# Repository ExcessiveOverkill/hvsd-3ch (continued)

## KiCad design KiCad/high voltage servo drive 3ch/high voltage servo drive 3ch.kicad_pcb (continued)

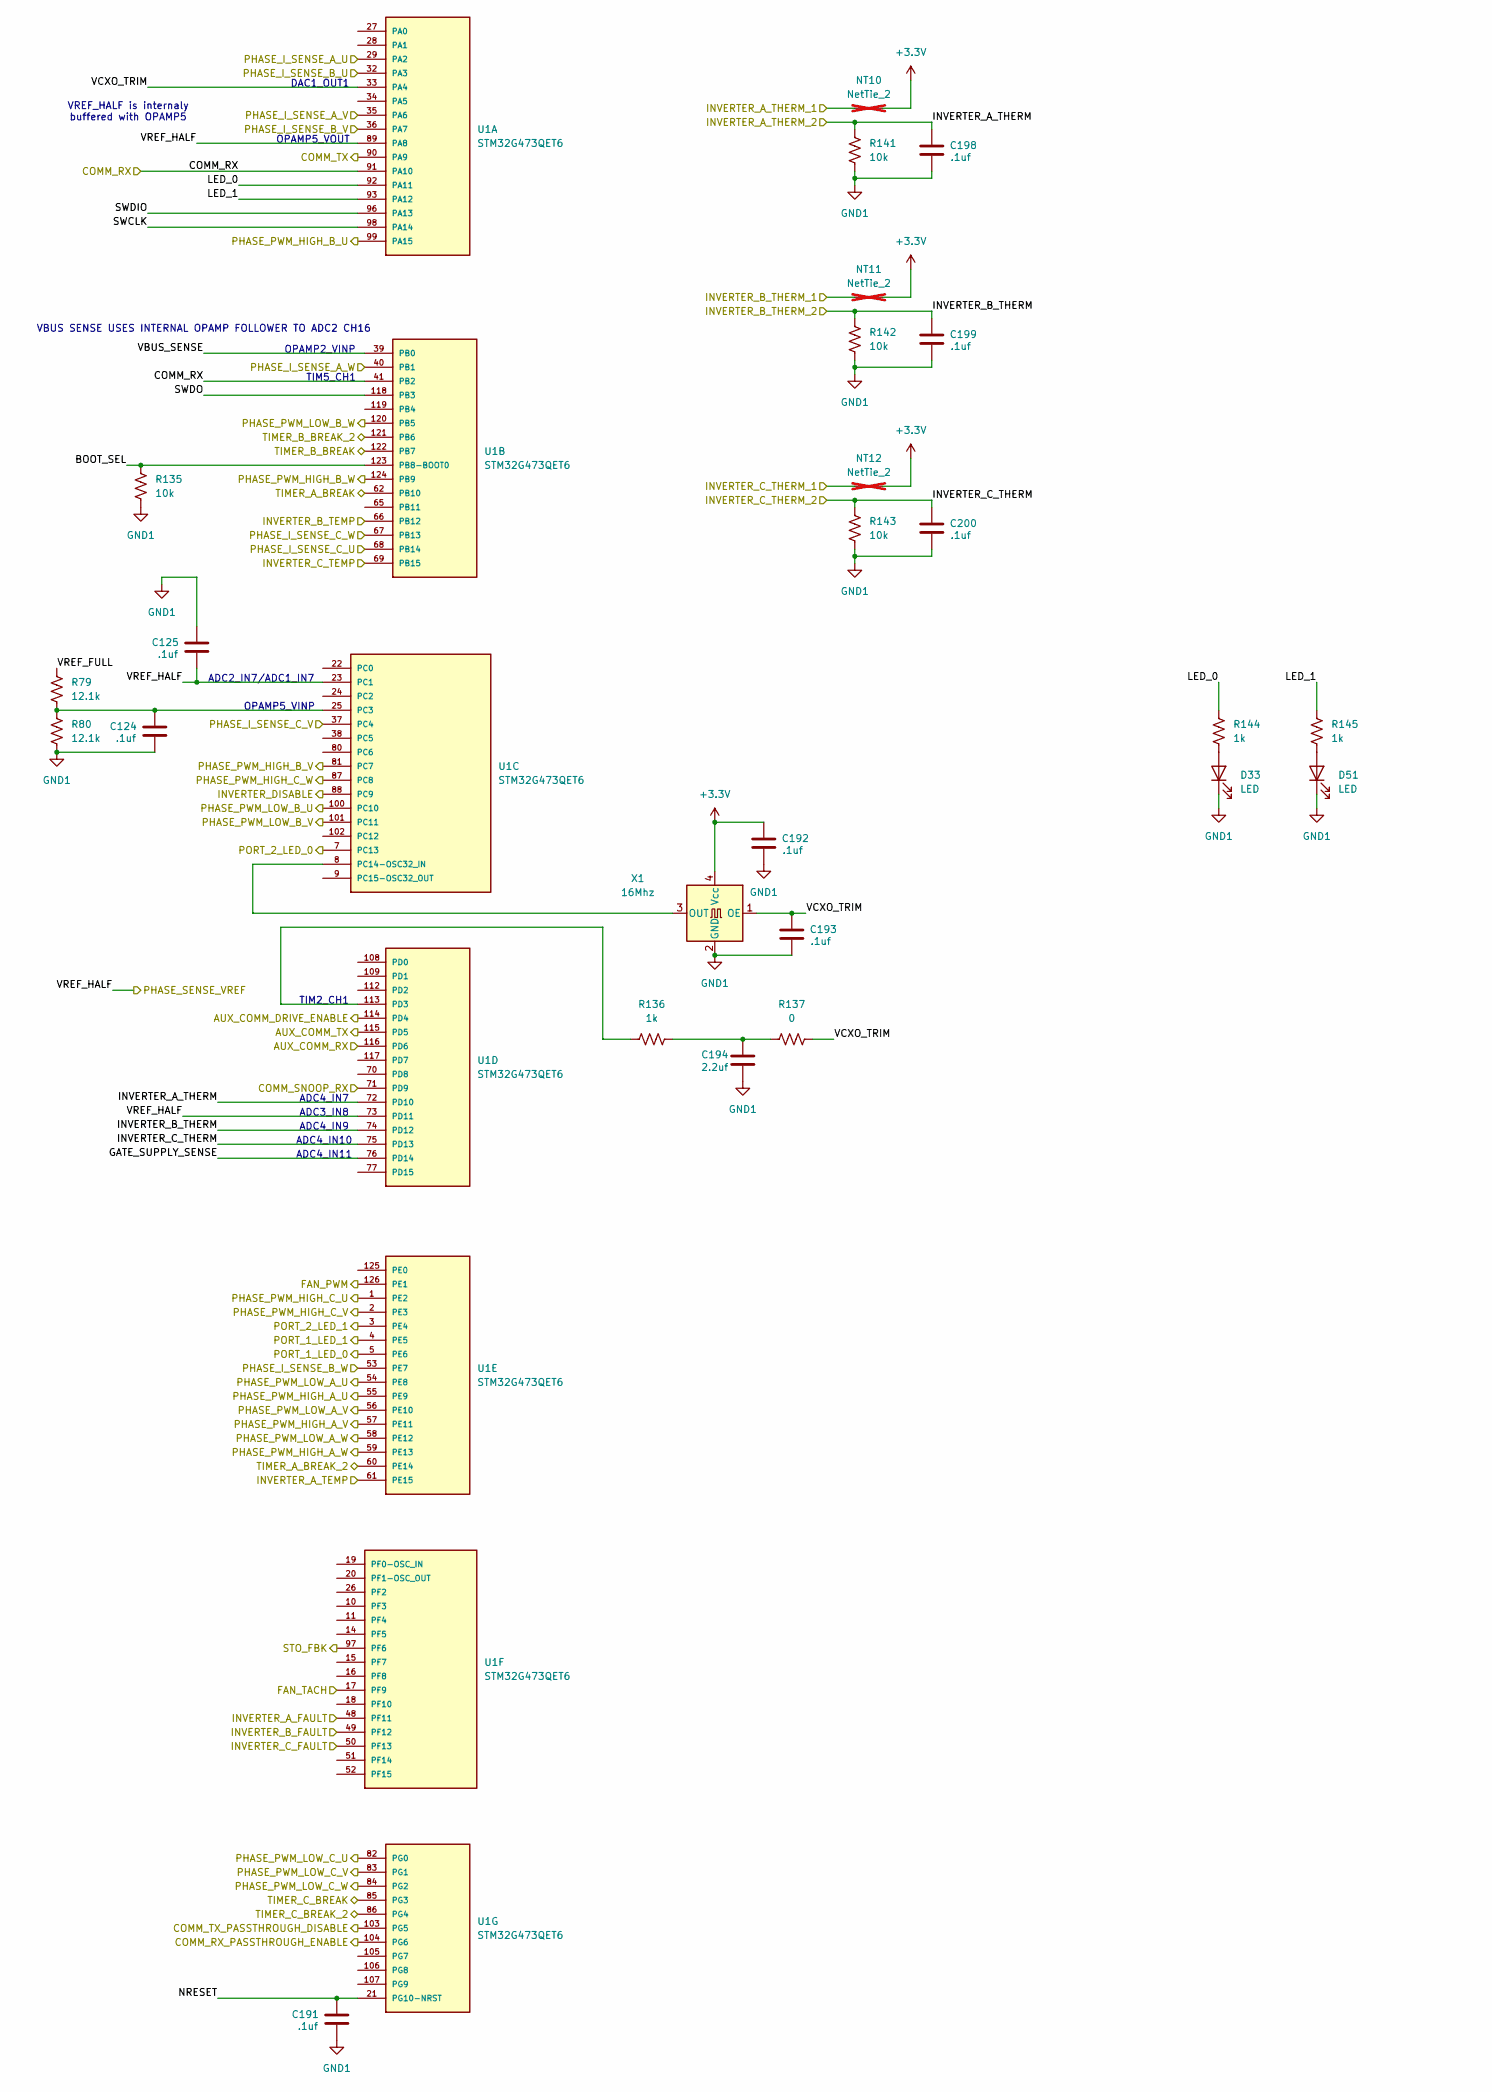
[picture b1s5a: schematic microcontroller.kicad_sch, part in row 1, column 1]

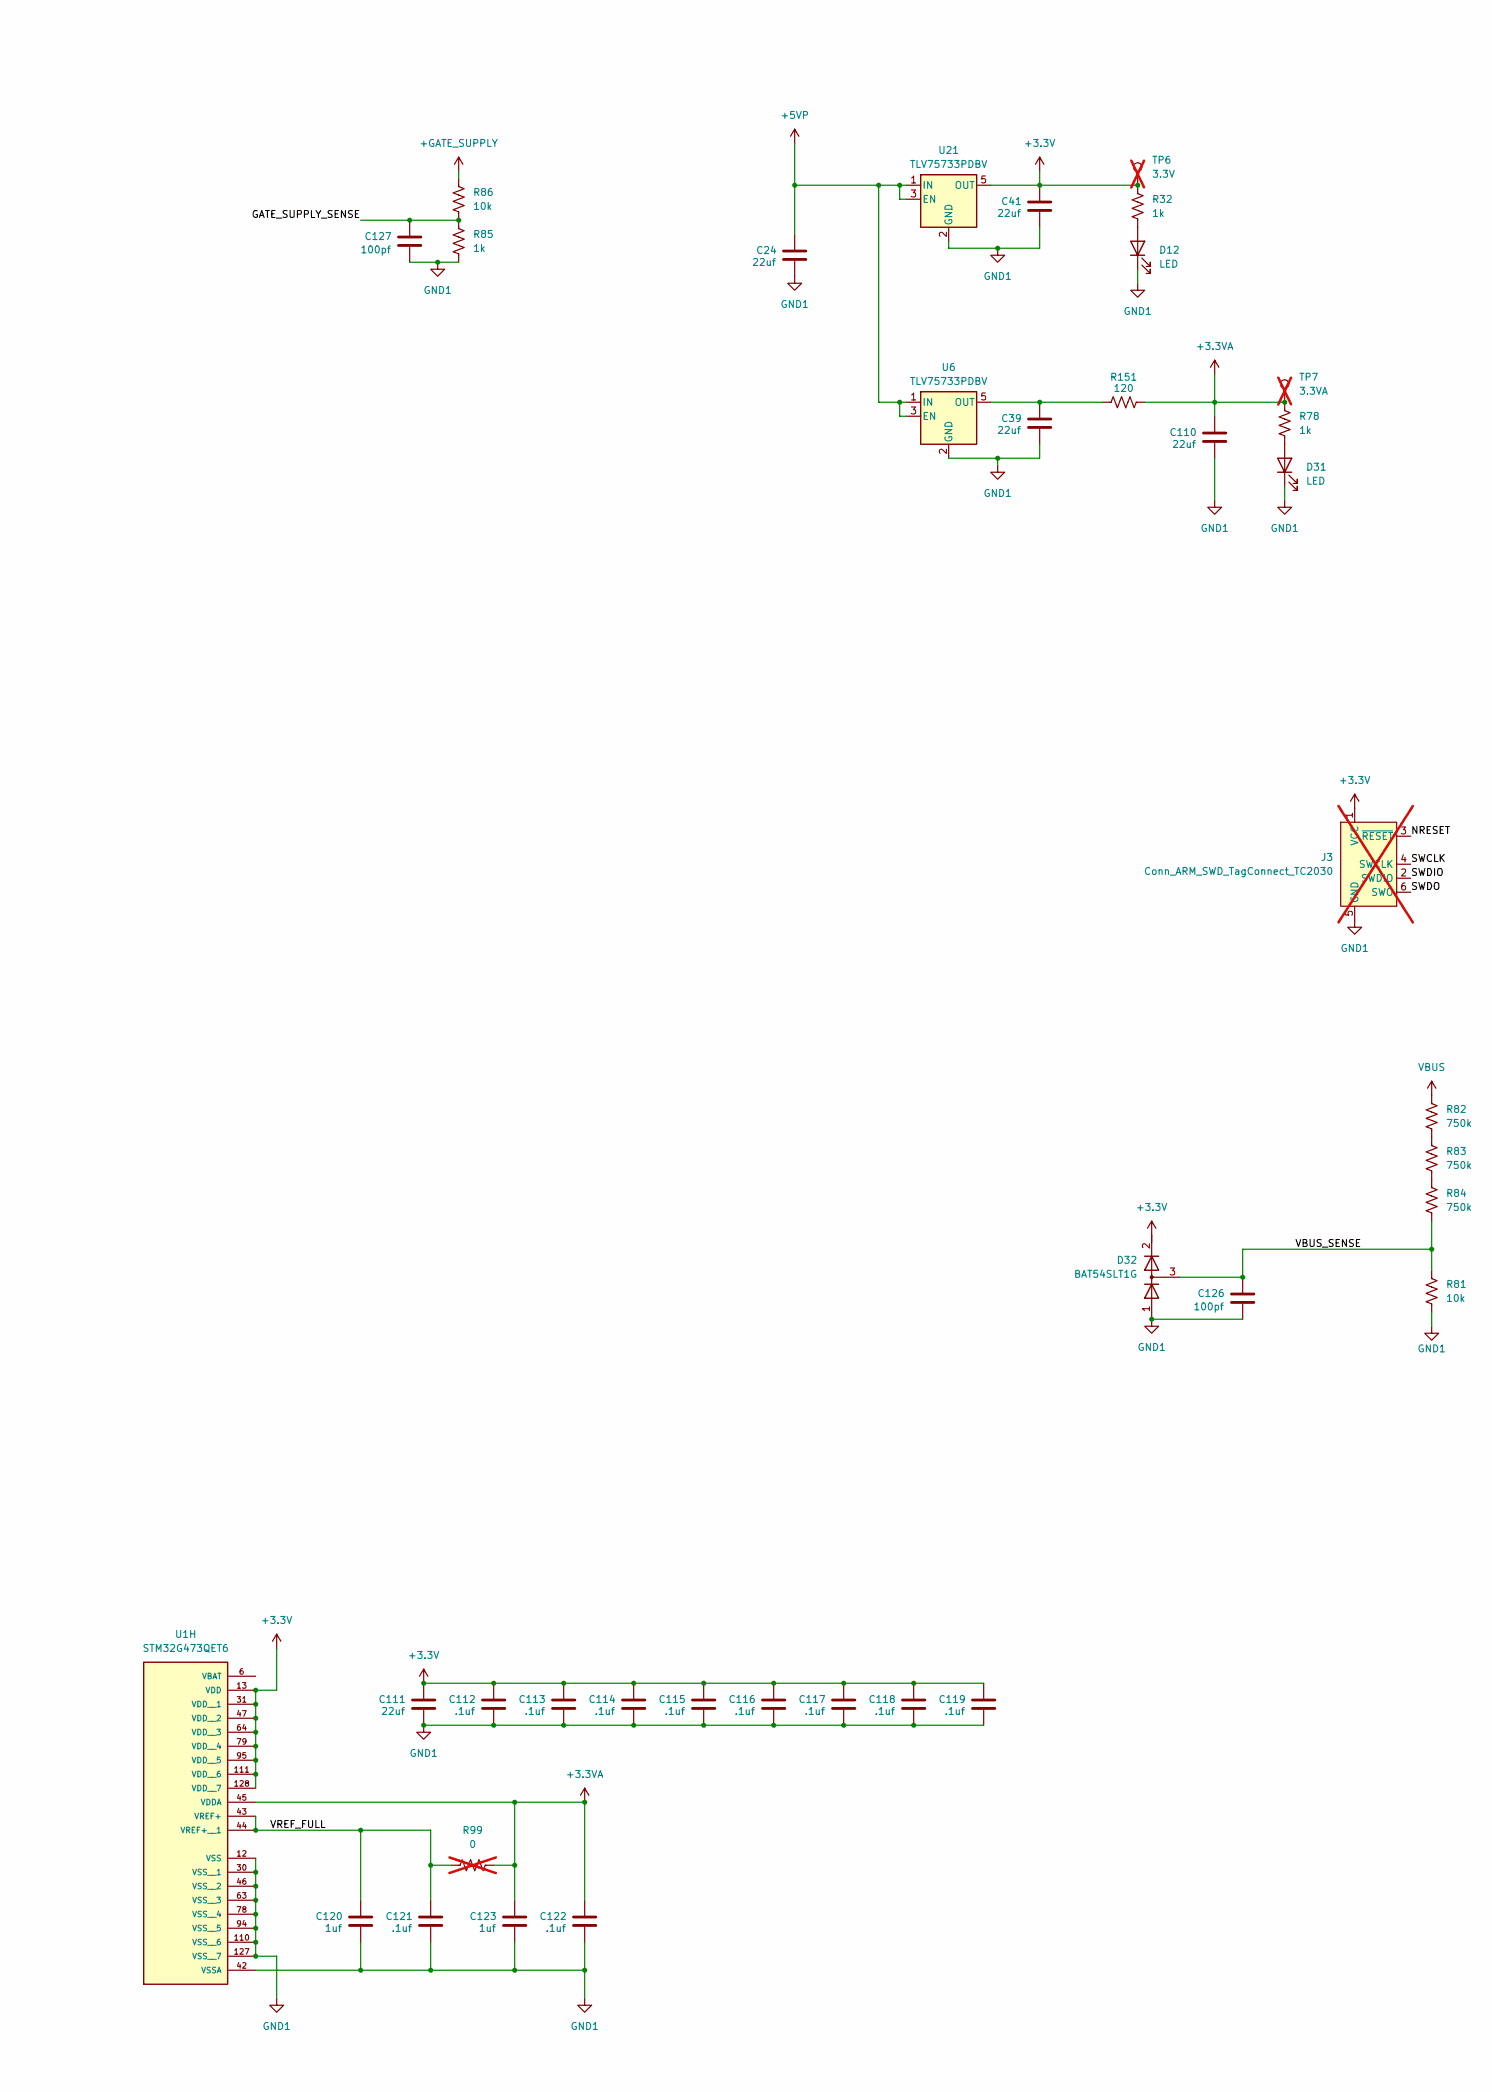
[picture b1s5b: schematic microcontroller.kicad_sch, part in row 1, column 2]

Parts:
C24, C39, C41, C110, C111: 22uf; C_1206_3216Metric; Part number CL31A226KAHNNNE; LCSC# C12891
C112, C113, C114, C115, C116, C117, C118, C119, C121, C122, C124, C125, C191, C192, C193, C198, C199, C200: .1uf; C_0402_1005Metric; Part number CC0402KRX5R9BB104; LCSC# C105882
C120, C123: 1uf; C_0402_1005Metric; Part number CL05A105KP5NNNC; LCSC# C14445
C126, C127: 100pf; C_0402_1005Metric; Part number CC0402JRNPO9BN101; LCSC# C106200
C194: 2.2uf; C_1206_3216Metric; Part number CL31B225KBHNNNE; LCSC# C50254
D12, D31, D33, D51: LED; LED_0603_1608Metric; Part number XL-1608UBC-04; LCSC# C965807
D32: BAT54SLT1G; SOT-23; Part number LBAT54SLT1G; LCSC# C12765
J3: Conn_ARM_SWD_TagConnect_TC2030; Tag-Connect_TC2030-IDC-FP_2x03_P1.27mm_Vertical; not fitted
NT10, NT11, NT12: NetTie_2; NetTie-2_SMD_Pad0.2mm; not fitted
R32, R78, R85, R136, R144, R145: 1k; R_0402_1005Metric; Part number RC0402FR-071KL; LCSC# C106235
R79, R80: 12.1k; R_0402_1005Metric; Part number RC0402FR-0712K1L; LCSC# C132157
R81, R86, R135, R141, R142, R143: 10k; R_0402_1005Metric; Part number RC0402FR-0710KL; LCSC# C60490
R82, R83, R84: 750k; R_1206_3216Metric; Part number RC1206FR-07750KL; LCSC# C137235
R99: 0; R_0402_1005Metric; Part number RC0402FR-070RL; LCSC# C106231; not fitted
R137: 0; R_0402_1005Metric; Part number RC0402FR-070RL; LCSC# C106231
R151: 120; R_0402_1005Metric; Part number RC0402FR-07120RL; LCSC# C114758
TP6: 3.3V; TestPoint_Pad_D2.0mm; not fitted
TP7: 3.3VA; TestPoint_Pad_D2.0mm; not fitted
U1: STM32G473QET6; QFP40P1600X1600X160-128N; PARTREV 4
U6, U21: TLV75733PDBV; SOT-23-5; Part number TLV75733PDBVR; LCSC# C485517
X1: 16Mhz; Oscillator_SMD_SeikoEpson_SG8002CE-4Pin_3.2x2.5mm; Part number SG-8002CE 16.000000MHz PHM; LCSC# C390318

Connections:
+3.3V: C41.2, C111.2, C112.2, C113.2, C114.2, C115.2, C116.2, C117.2, C118.2, C119.2, C192.2, D32.2 (K), J3.1 (VCC), NT10.2, NT11.2, NT12.2, R32.2, TP6.1, U1.13 (VDD), U1.31 (VDD__1), U1.47 (VDD__2), U1.64 (VDD__3), U1.79 (VDD__4), U1.95 (VDD__5), U1.111 (VDD__6), U1.128 (VDD__7), U21.5 (OUT), X1.4 (Vcc); also elsewhere on the board
+3.3VA: C110.2, C122.2, C123.2, R78.2, R99.2, R151.2, TP7.1, U1.45 (VDDA); also elsewhere on the board
+5VP: C24.2, U6.1 (IN), U6.3 (EN), U21.1 (IN), U21.3 (EN); also elsewhere on the board
+GATE_SUPPLY: R86.2; also elsewhere on the board
/Communication/FAN_PWM: U1.126 (PE1); also elsewhere on the board
/Communication/FAN_TACH: U1.17 (PF9); also elsewhere on the board
/Communication/J1_LED0: U1.5 (PE6); also elsewhere on the board
/Communication/J1_LED1: U1.4 (PE5); also elsewhere on the board
/Communication/J2_LED0: U1.3 (PE4); also elsewhere on the board
/Communication/J2_LED1: U1.7 (PC13); also elsewhere on the board
/Communication/RX_PASSTHROUGH_ENABLE: U1.104 (PG6); also elsewhere on the board
/Communication/TX: U1.90 (PA9); also elsewhere on the board
/Communication/TX_PASSTHROUGH_DISABLE: U1.103 (PG5); also elsewhere on the board
/Communication/TX_SNOOP: U1.71 (PD9); also elsewhere on the board
/Current Sense/SENSE_A_U: U1.29 (PA2); also elsewhere on the board
/Current Sense/SENSE_A_V: U1.35 (PA6); also elsewhere on the board
/Current Sense/SENSE_A_W: U1.40 (PB1); also elsewhere on the board
/Current Sense/SENSE_B_U: U1.32 (PA3); also elsewhere on the board
/Current Sense/SENSE_B_V: U1.36 (PA7); also elsewhere on the board
/Current Sense/SENSE_B_W: U1.53 (PE7); also elsewhere on the board
/Current Sense/SENSE_C_U: U1.68 (PB14); also elsewhere on the board
/Current Sense/SENSE_C_V: U1.37 (PC4); also elsewhere on the board
/Current Sense/SENSE_C_W: U1.67 (PB13); also elsewhere on the board
/INVERTER_A_FAULT: U1.48 (PF11); also elsewhere on the board
/INVERTER_A_TEMP: U1.61 (PE15); also elsewhere on the board
/INVERTER_B_FAULT: U1.49 (PF12); also elsewhere on the board
/INVERTER_B_TEMP: U1.66 (PB12); also elsewhere on the board
/INVERTER_C_FAULT: U1.50 (PF13); also elsewhere on the board
/INVERTER_C_TEMP: U1.69 (PB15); also elsewhere on the board
/Inverter A/THERM_1: NT10.1; also elsewhere on the board
/Inverter B/THERM_1: NT11.1; also elsewhere on the board
/Inverter C/THERM_1: NT12.1; also elsewhere on the board
/MOTOR_A.HIN_U: U1.55 (PE9); also elsewhere on the board
/MOTOR_A.HIN_V: U1.57 (PE11); also elsewhere on the board
/MOTOR_A.HIN_W: U1.59 (PE13); also elsewhere on the board
/MOTOR_A.LIN_U: U1.54 (PE8); also elsewhere on the board
/MOTOR_A.LIN_V: U1.56 (PE10); also elsewhere on the board
/MOTOR_A.LIN_W: U1.58 (PE12); also elsewhere on the board
/MOTOR_B.HIN_U: U1.99 (PA15); also elsewhere on the board
/MOTOR_B.HIN_V: U1.81 (PC7); also elsewhere on the board
/MOTOR_B.HIN_W: U1.124 (PB9); also elsewhere on the board
/MOTOR_B.LIN_U: U1.100 (PC10); also elsewhere on the board
/MOTOR_B.LIN_V: U1.101 (PC11); also elsewhere on the board
/MOTOR_B.LIN_W: U1.120 (PB5); also elsewhere on the board
/MOTOR_C.HIN_U: U1.1 (PE2); also elsewhere on the board
/MOTOR_C.HIN_V: U1.2 (PE3); also elsewhere on the board
/MOTOR_C.HIN_W: U1.87 (PC8); also elsewhere on the board
/MOTOR_C.LIN_U: U1.82 (PG0); also elsewhere on the board
/MOTOR_C.LIN_V: U1.83 (PG1); also elsewhere on the board
/MOTOR_C.LIN_W: U1.84 (PG2); also elsewhere on the board
/Microcontroller/AUX_COMM_DRIVE_ENABLE: U1.114 (PD4)
/Microcontroller/AUX_COMM_RX: U1.116 (PD6)
/Microcontroller/AUX_COMM_TX: U1.115 (PD5)
/Microcontroller/BOOT_SEL: R135.2, U1.123 (PB8-BOOT0)
/Microcontroller/COMM_RX: U1.41 (PB2), U1.91 (PA10); also elsewhere on the board
/Microcontroller/GATE_SUPPLY_SENSE: C127.2, R85.2, R86.1, U1.76 (PD14)
/Microcontroller/INVERTER_A_THERM: C198.2, R141.1, U1.72 (PD10); also elsewhere on the board
/Microcontroller/INVERTER_B_THERM: C199.2, R142.1, U1.74 (PD12); also elsewhere on the board
/Microcontroller/INVERTER_C_THERM: C200.2, R143.1, U1.75 (PD13); also elsewhere on the board
/Microcontroller/INVERTER_DISABLE: U1.88 (PC9); also elsewhere on the board
/Microcontroller/LED_0: R144.2, U1.92 (PA11)
/Microcontroller/LED_1: R145.2, U1.93 (PA12)
/Microcontroller/NRESET: C191.2, J3.3 (~RESET), U1.21 (PG10-NRST)
/Microcontroller/SWCLK: J3.4 (SWCLK), U1.98 (PA14)
/Microcontroller/SWDIO: J3.2 (SWDIO), U1.96 (PA13)
/Microcontroller/SWDO: J3.6 (SWO), U1.118 (PB3)
/Microcontroller/VCXO_TRIM: C193.2, R137.1, U1.33 (PA4), X1.1 (OE)
/Microcontroller/VREF_FULL: C120.2, C121.2, R79.1, R99.1, U1.43 (VREF+), U1.44 (VREF+__1)
/Microcontroller/VREF_HALF: C125.1, U1.23 (PC1), U1.73 (PD11), U1.89 (PA8); also elsewhere on the board
/PWM_DISABLE_1: U1.62 (PB10), U1.85 (PG3), U1.122 (PB7); also elsewhere on the board
/PWM_DISABLE_2: U1.60 (PE14), U1.86 (PG4), U1.121 (PB6); also elsewhere on the board
/STO_FBK: U1.97 (PF6); also elsewhere on the board
unnamed: C194.2, R136.1, R137.2
unnamed: D12.2 (A), R32.1
unnamed: D31.2 (A), R78.1
unnamed: D33.2 (A), R144.1
unnamed: D51.2 (A), R145.1
unnamed: R82.2, R83.1
unnamed: R83.2, R84.1
unnamed: C124.2, R79.2, R80.1, U1.25 (PC3)
unnamed: R136.2, U1.113 (PD3)
unnamed 235: C39.2, R151.1, U6.5 (OUT); also elsewhere on the board
VBUS: R82.1; also elsewhere on the board

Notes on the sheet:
ADC3_IN8
VREF_HALF is internaly buffered with OPAMP5
ADC4_IN9
ADC2_IN7/ADC1_IN7
VBUS SENSE USES INTERNAL OPAMP FOLLOWER TO ADC2 CH16
ADC4_IN7
TIM5_CH1
ADC4_IN11
OPAMP2_VINP
OPAMP5_VOUT
ADC4_IN10
OPAMP5_VINP
TIM2_CH1
DAC1_OUT1

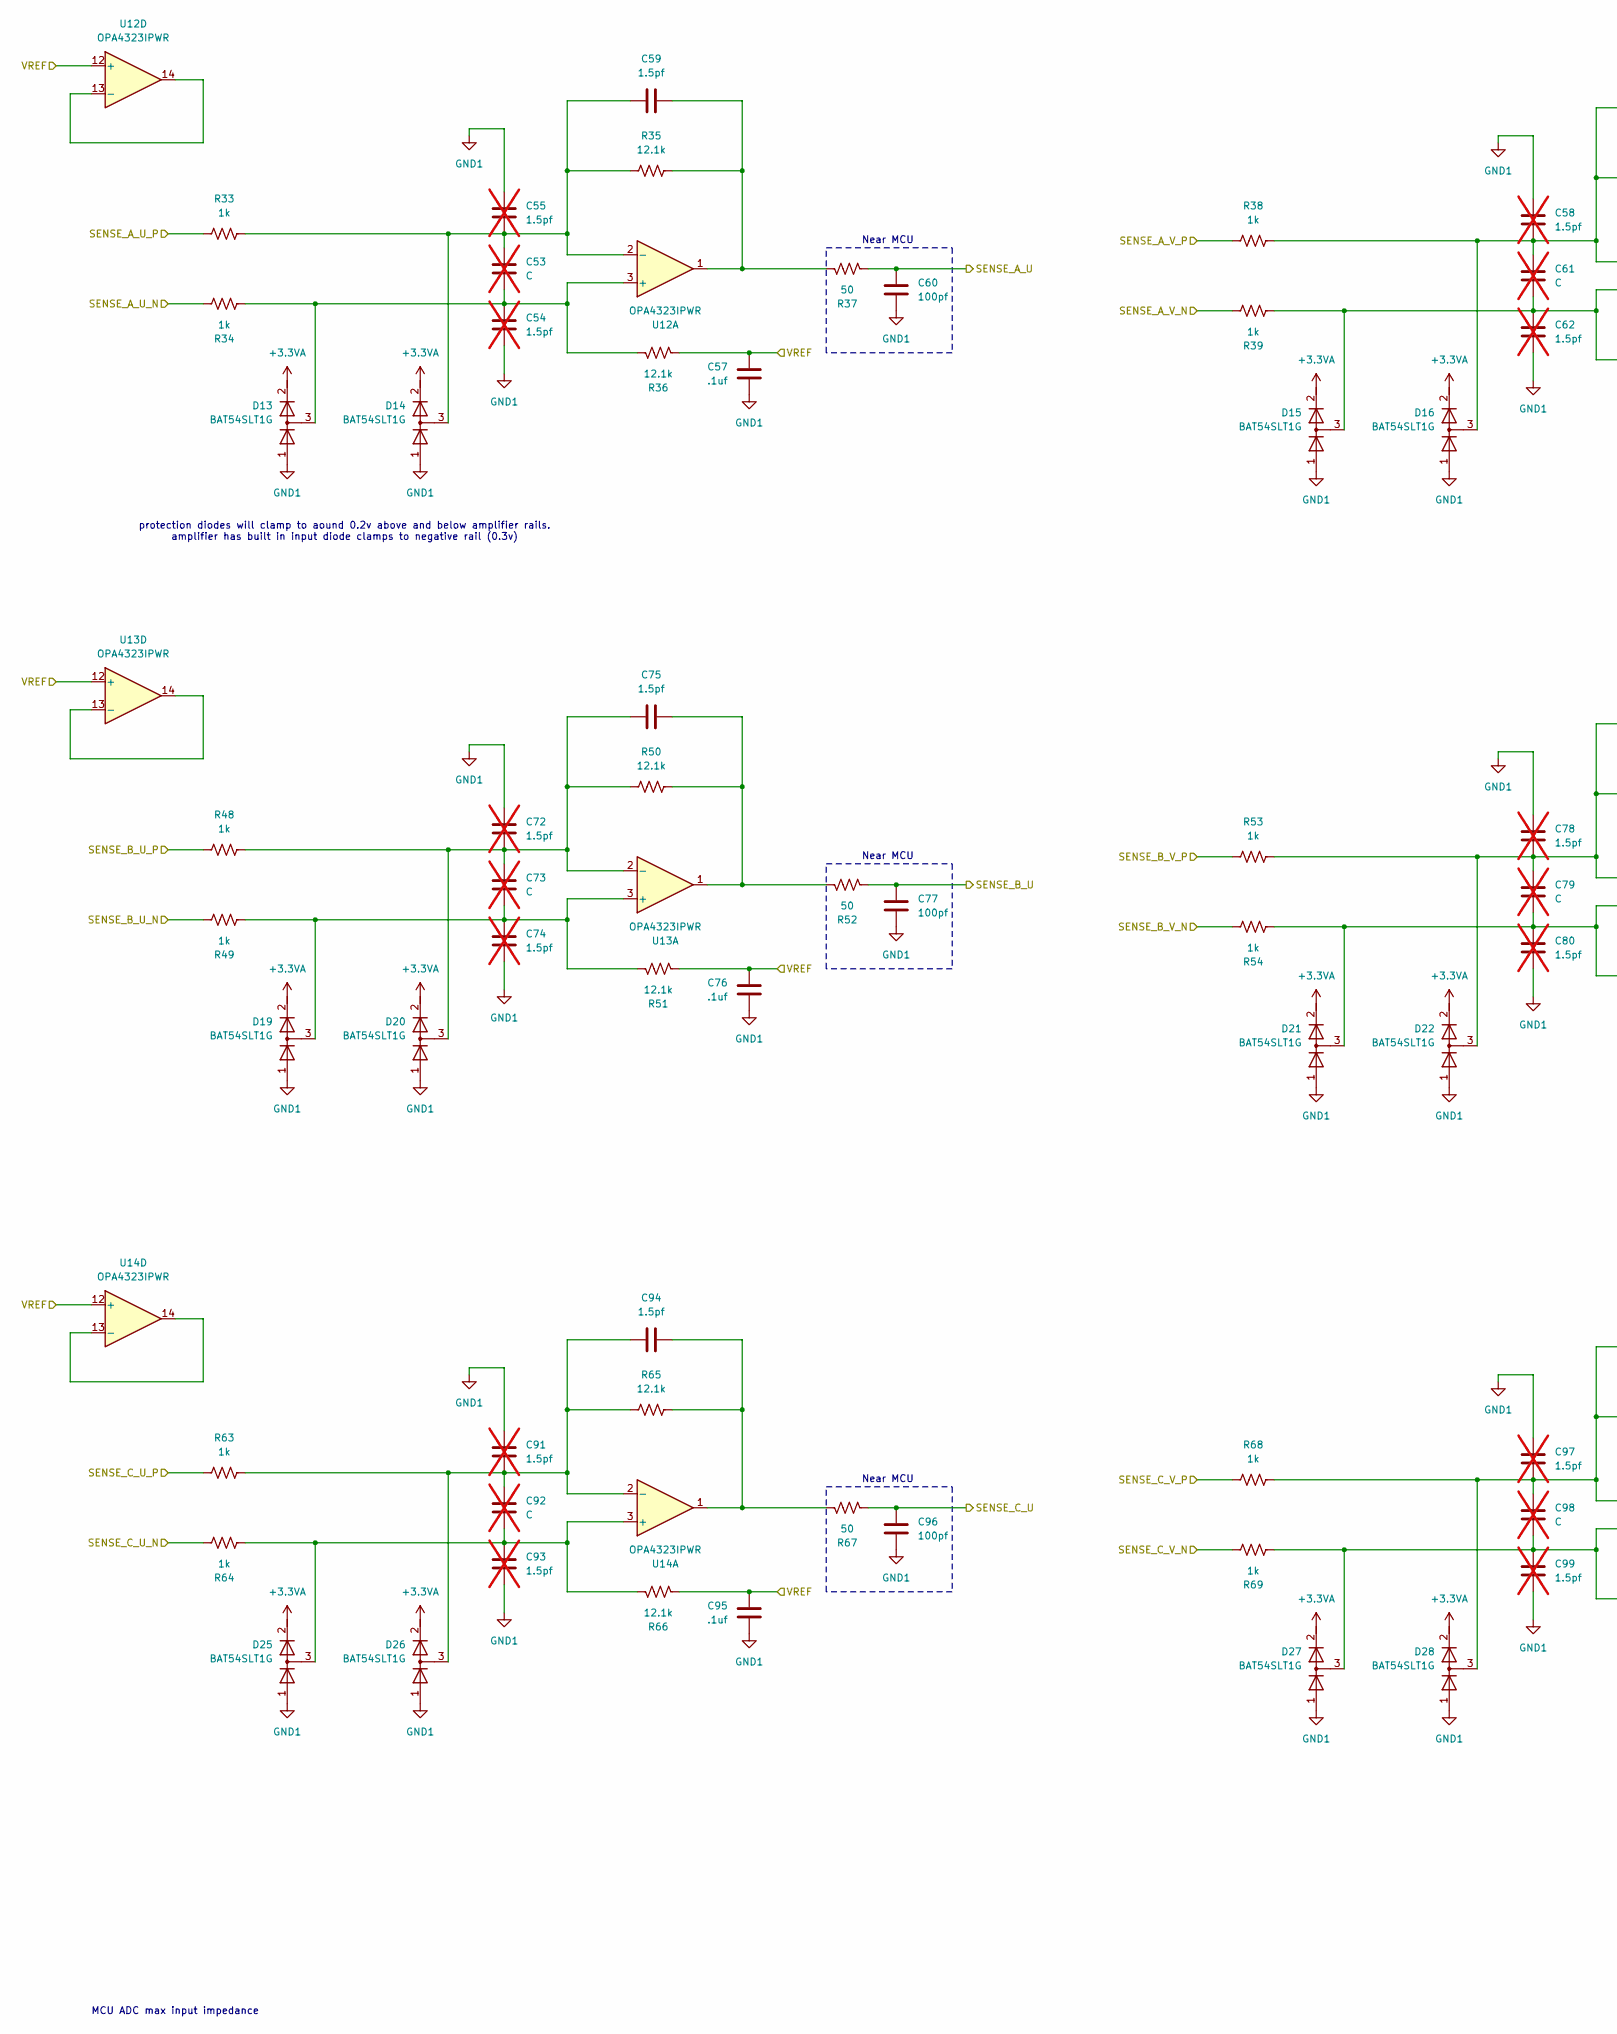
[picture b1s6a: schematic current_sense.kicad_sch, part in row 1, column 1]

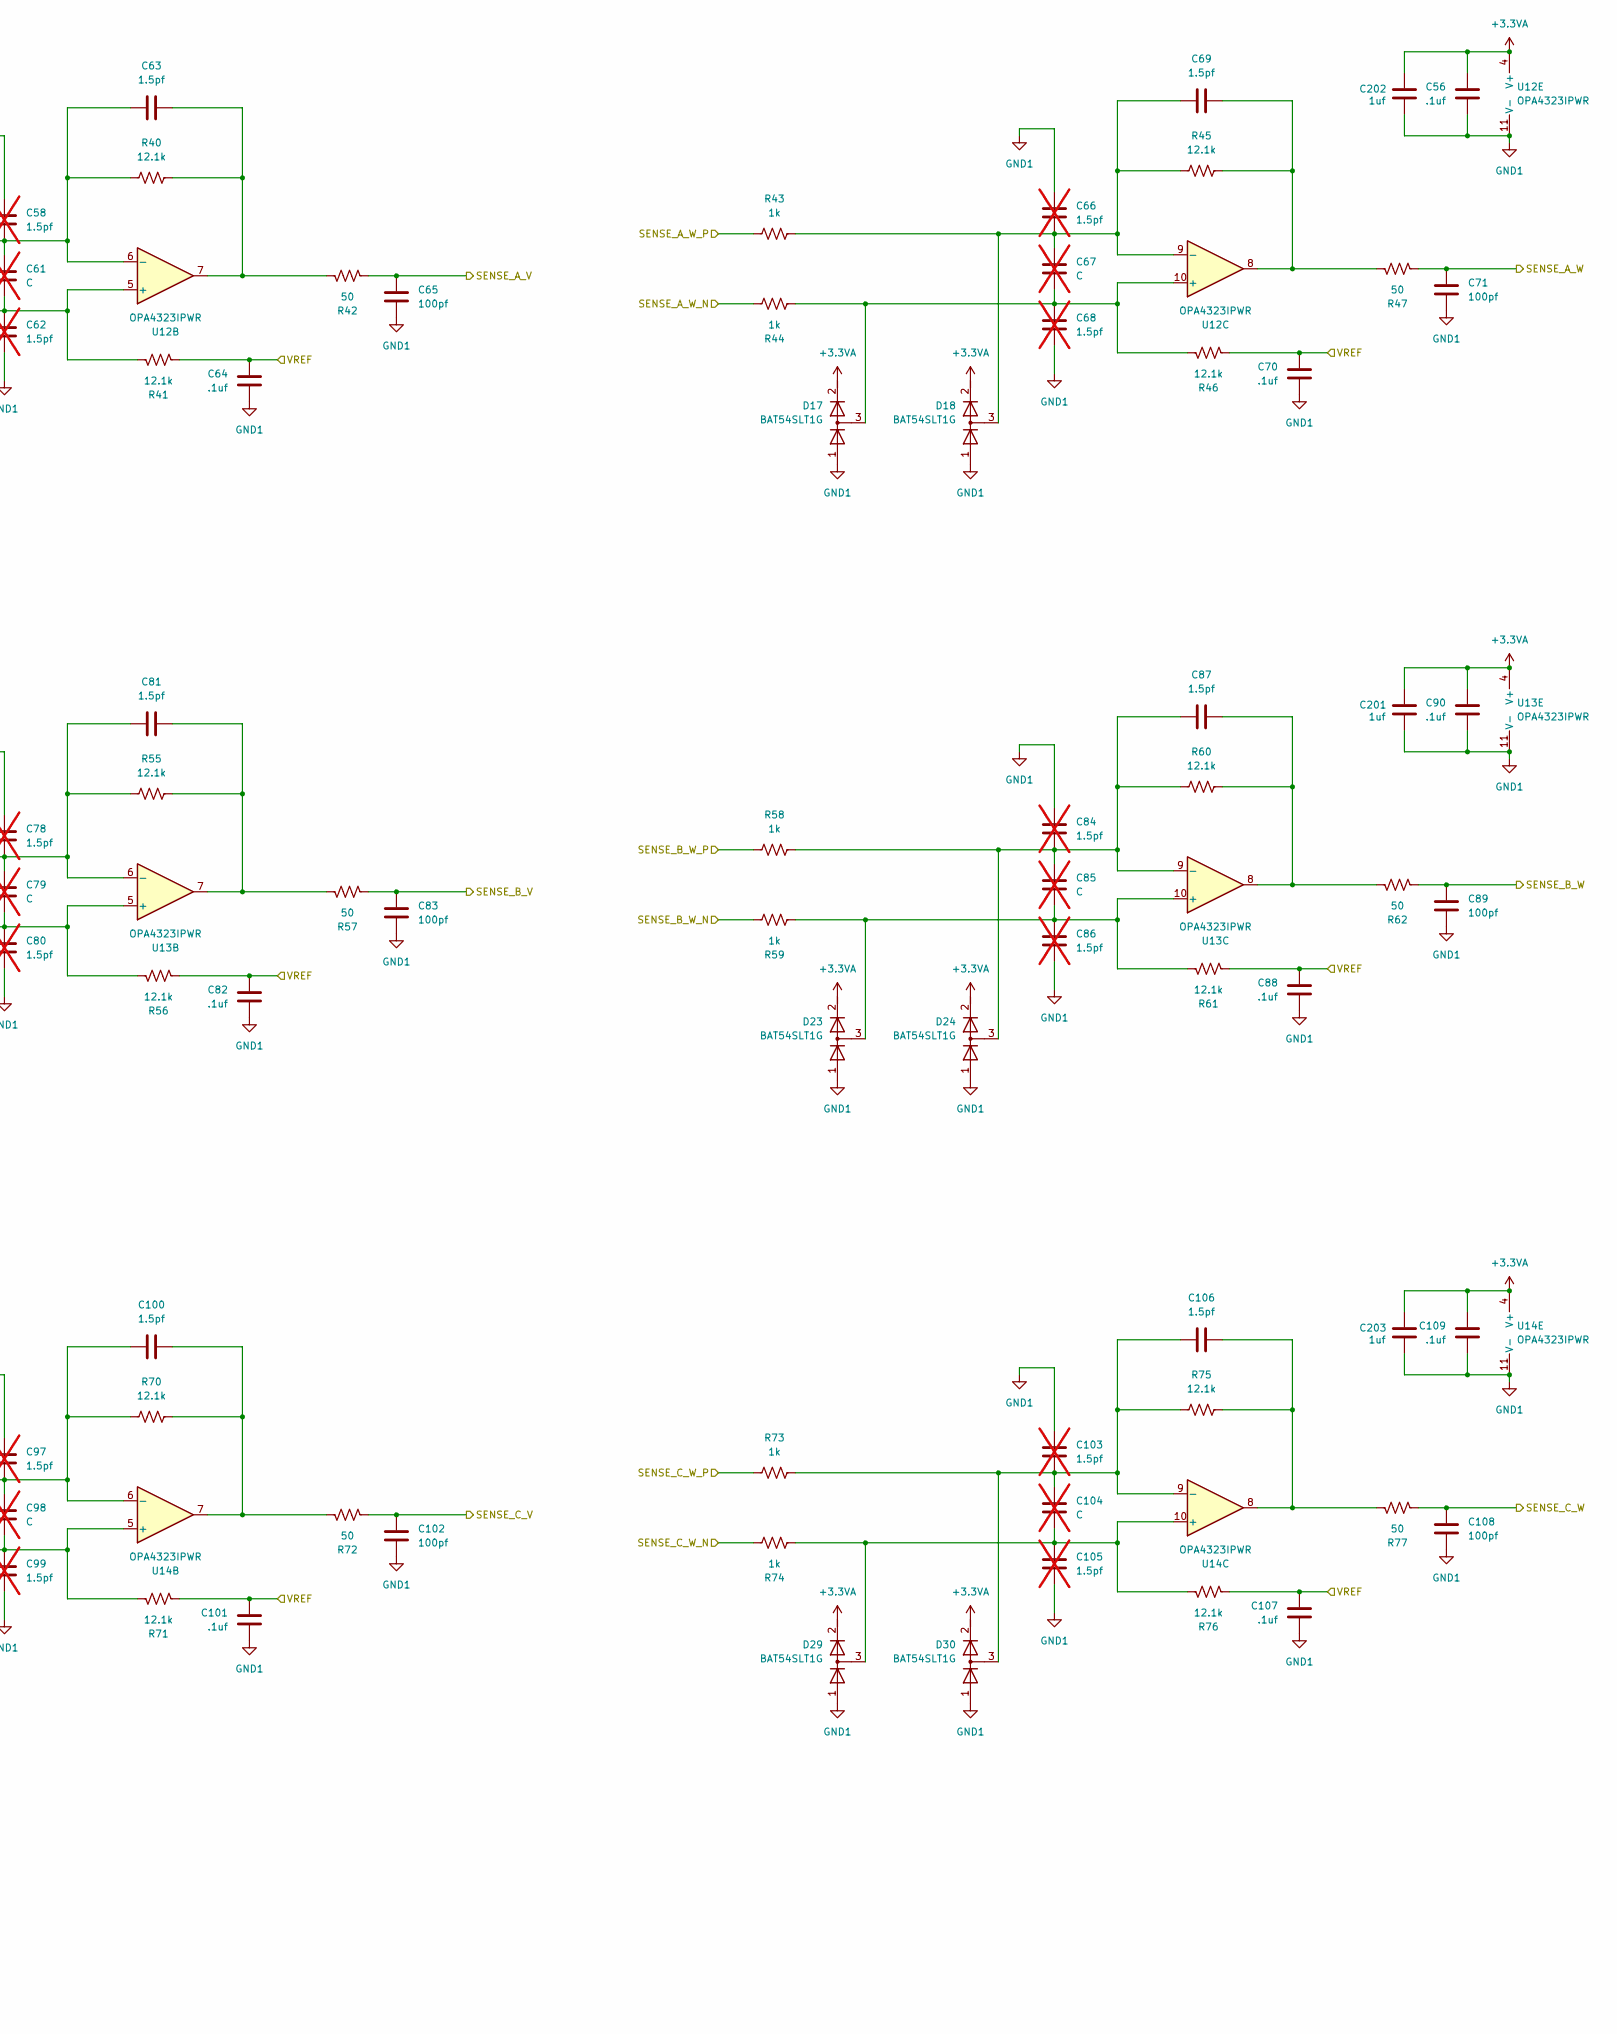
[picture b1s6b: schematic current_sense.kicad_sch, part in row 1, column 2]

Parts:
C53, C61, C67, C73, C79, C85, C92, C98, C104: C; C_0402_1005Metric; not fitted
C54, C55, C58, C62, C66, C68, C72, C74, C78, C80, C84, C86, C91, C93, C97, C99, C103, C105: 1.5pf; C_0402_1005Metric; Part number CC0402BRNPO9BN1R5; LCSC# C282238; not fitted
C56, C57, C64, C70, C76, C82, C88, C90, C95, C101, C107, C109: .1uf; C_0402_1005Metric; Part number CC0402KRX5R9BB104; LCSC# C105882
C59, C63, C69, C75, C81, C87, C94, C100, C106: 1.5pf; C_0402_1005Metric; Part number CC0402BRNPO9BN1R5; LCSC# C282238
C60, C65, C71, C77, C83, C89, C96, C102, C108: 100pf; C_0402_1005Metric; Part number CC0402JRNPO9BN101; LCSC# C106200
C201, C202, C203: 1uf; C_0402_1005Metric; Part number CL05A105KP5NNNC; LCSC# C14445
D13, D14, D15, D16, D17, D18, D19, D20, D21, D22, D23, D24, D25, D26, D27, D28, D29, D30: BAT54SLT1G; SOT-23; Part number LBAT54SLT1G; LCSC# C12765
R33, R34, R38, R39, R43, R44, R48, R49, R53, R54, R58, R59, R63, R64, R68, R69, R73, R74: 1k; R_0402_1005Metric; Part number RC0402FR-071KL; LCSC# C106235
R35, R36, R40, R41, R45, R46, R50, R51, R55, R56, R60, R61, R65, R66, R70, R71, R75, R76: 12.1k; R_0402_1005Metric; Part number RC0402FR-0712K1L; LCSC# C132157
R37, R42, R47, R52, R57, R62, R67, R72, R77: 50; R_0402_1005Metric; Part number RC0402JR-0750RL; LCSC# C477760
U12, U13, U14: OPA4323IPWR; TSSOP-14_4.4x5mm_P0.65mm; Part number OPA4323IPWR; LCSC# C22419728

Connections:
+3.3VA: C56.1, C90.1, C109.1, C201.2, C202.2, C203.2, D13.2 (K), D14.2 (K), D15.2 (K), D16.2 (K), D17.2 (K), D18.2 (K), D19.2 (K), D20.2 (K), D21.2 (K), D22.2 (K), D23.2 (K), D24.2 (K), D25.2 (K), D26.2 (K), D27.2 (K), D28.2 (K), D29.2 (K), D30.2 (K), U12.4 (V+), U13.4 (V+), U14.4 (V+); also elsewhere on the board
/Current Sense/SENSE_A_U: C60.1, R37.2; also elsewhere on the board
/Current Sense/SENSE_A_V: C65.1, R42.2; also elsewhere on the board
/Current Sense/SENSE_A_W: C71.1, R47.2; also elsewhere on the board
/Current Sense/SENSE_B_U: C77.1, R52.2; also elsewhere on the board
/Current Sense/SENSE_B_V: C83.1, R57.2; also elsewhere on the board
/Current Sense/SENSE_B_W: C89.1, R62.2; also elsewhere on the board
/Current Sense/SENSE_C_U: C96.1, R67.2; also elsewhere on the board
/Current Sense/SENSE_C_V: C102.1, R72.2; also elsewhere on the board
/Current Sense/SENSE_C_W: C108.1, R77.2; also elsewhere on the board
/MOTOR_A.U_N: R34.2; also elsewhere on the board
/MOTOR_A.U_P: R33.1; also elsewhere on the board
/MOTOR_A.V_N: R39.2; also elsewhere on the board
/MOTOR_A.V_P: R38.1; also elsewhere on the board
/MOTOR_A.W_N: R44.2; also elsewhere on the board
/MOTOR_A.W_P: R43.1; also elsewhere on the board
/MOTOR_B.U_N: R49.2; also elsewhere on the board
/MOTOR_B.U_P: R48.1; also elsewhere on the board
/MOTOR_B.V_N: R54.2; also elsewhere on the board
/MOTOR_B.V_P: R53.1; also elsewhere on the board
/MOTOR_B.W_N: R59.2; also elsewhere on the board
/MOTOR_B.W_P: R58.1; also elsewhere on the board
/MOTOR_C.U_N: R64.2; also elsewhere on the board
/MOTOR_C.U_P: R63.1; also elsewhere on the board
/MOTOR_C.V_N: R69.2; also elsewhere on the board
/MOTOR_C.V_P: R68.1; also elsewhere on the board
/MOTOR_C.W_N: R74.2; also elsewhere on the board
/MOTOR_C.W_P: R73.1; also elsewhere on the board
/Microcontroller/VREF_HALF: C57.1, C64.1, C70.1, C76.1, C82.1, C88.1, C95.1, C101.1, C107.1, R36.2, R41.2, R46.2, R51.2, R56.2, R61.2, R66.2, R71.2, R76.2, U12.12 (+), U13.12 (+), U14.12 (+); also elsewhere on the board
unnamed: C59.2, R35.2, R37.1, U12.1
unnamed: C63.2, R40.2, R42.1, U12.7
unnamed: C69.2, R45.2, R47.1, U12.8
unnamed: C75.2, R50.2, R52.1, U13.1
unnamed: C81.2, R55.2, R57.1, U13.7
unnamed: C87.2, R60.2, R62.1, U13.8
unnamed: C94.2, R65.2, R67.1, U14.1
unnamed: C100.2, R70.2, R72.1, U14.7
unnamed: C106.2, R75.2, R77.1, U14.8
unnamed: C53.2, C54.1, D13.3 (common), R34.1, R36.1, U12.3 (+)
unnamed: C53.1, C55.2, C59.1, D14.3 (common), R33.2, R35.1, U12.2 (-)
unnamed: C61.2, C62.1, D15.3 (common), R39.1, R41.1, U12.5 (+)
unnamed: C58.2, C61.1, C63.1, D16.3 (common), R38.2, R40.1, U12.6 (-)
unnamed: C67.2, C68.1, D17.3 (common), R44.1, R46.1, U12.10 (+)
unnamed: C66.2, C67.1, C69.1, D18.3 (common), R43.2, R45.1, U12.9 (-)
unnamed: C73.2, C74.1, D19.3 (common), R49.1, R51.1, U13.3 (+)
unnamed: C72.2, C73.1, C75.1, D20.3 (common), R48.2, R50.1, U13.2 (-)
unnamed: C79.2, C80.1, D21.3 (common), R54.1, R56.1, U13.5 (+)
unnamed: C78.2, C79.1, C81.1, D22.3 (common), R53.2, R55.1, U13.6 (-)
unnamed: C85.2, C86.1, D23.3 (common), R59.1, R61.1, U13.10 (+)
unnamed: C84.2, C85.1, C87.1, D24.3 (common), R58.2, R60.1, U13.9 (-)
unnamed: C92.2, C93.1, D25.3 (common), R64.1, R66.1, U14.3 (+)
unnamed: C91.2, C92.1, C94.1, D26.3 (common), R63.2, R65.1, U14.2 (-)
unnamed: C98.2, C99.1, D27.3 (common), R69.1, R71.1, U14.5 (+)
unnamed: C97.2, C98.1, C100.1, D28.3 (common), R68.2, R70.1, U14.6 (-)
unnamed: C104.2, C105.1, D29.3 (common), R74.1, R76.1, U14.10 (+)
unnamed: C103.2, C104.1, C106.1, D30.3 (common), R73.2, R75.1, U14.9 (-)
unnamed: U12.13 (-), U12.14
unnamed: U13.13 (-), U13.14
unnamed: U14.13 (-), U14.14

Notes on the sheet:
protection diodes will clamp to aound 0.2v above and below amplifier rails. amplifier has built in input diode clamps to negative rail (0.3v)
Near MCU
MCU ADC max input impedance
